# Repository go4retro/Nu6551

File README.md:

# Nu6551 

An implementation of the MOS 6551 Asynchronous Communications Interface Adapter (ACIA) that utilizes a small CPLD and an Atmel AVR ATMEGA88/168 microcontroller

## Introduction

## Technical Details

## License
Copyright (C) 2018-20  RETRO Innovations

These files are free designs; you can redistribute them and/or modify
them under the terms of the Creative Commons Attribution-ShareAlike 
4.0 International License.

You should have received a copy of the license along with this
work. If not, see <http://creativecommons.org/licenses/by-sa/4.0/>.

These files are distributed in the hope that they will be useful,
but WITHOUT ANY WARRANTY; without even the implied warranty of
MERCHANTABILITY or FITNESS FOR A PARTICULAR PURPOSE.  See the
license for more details.

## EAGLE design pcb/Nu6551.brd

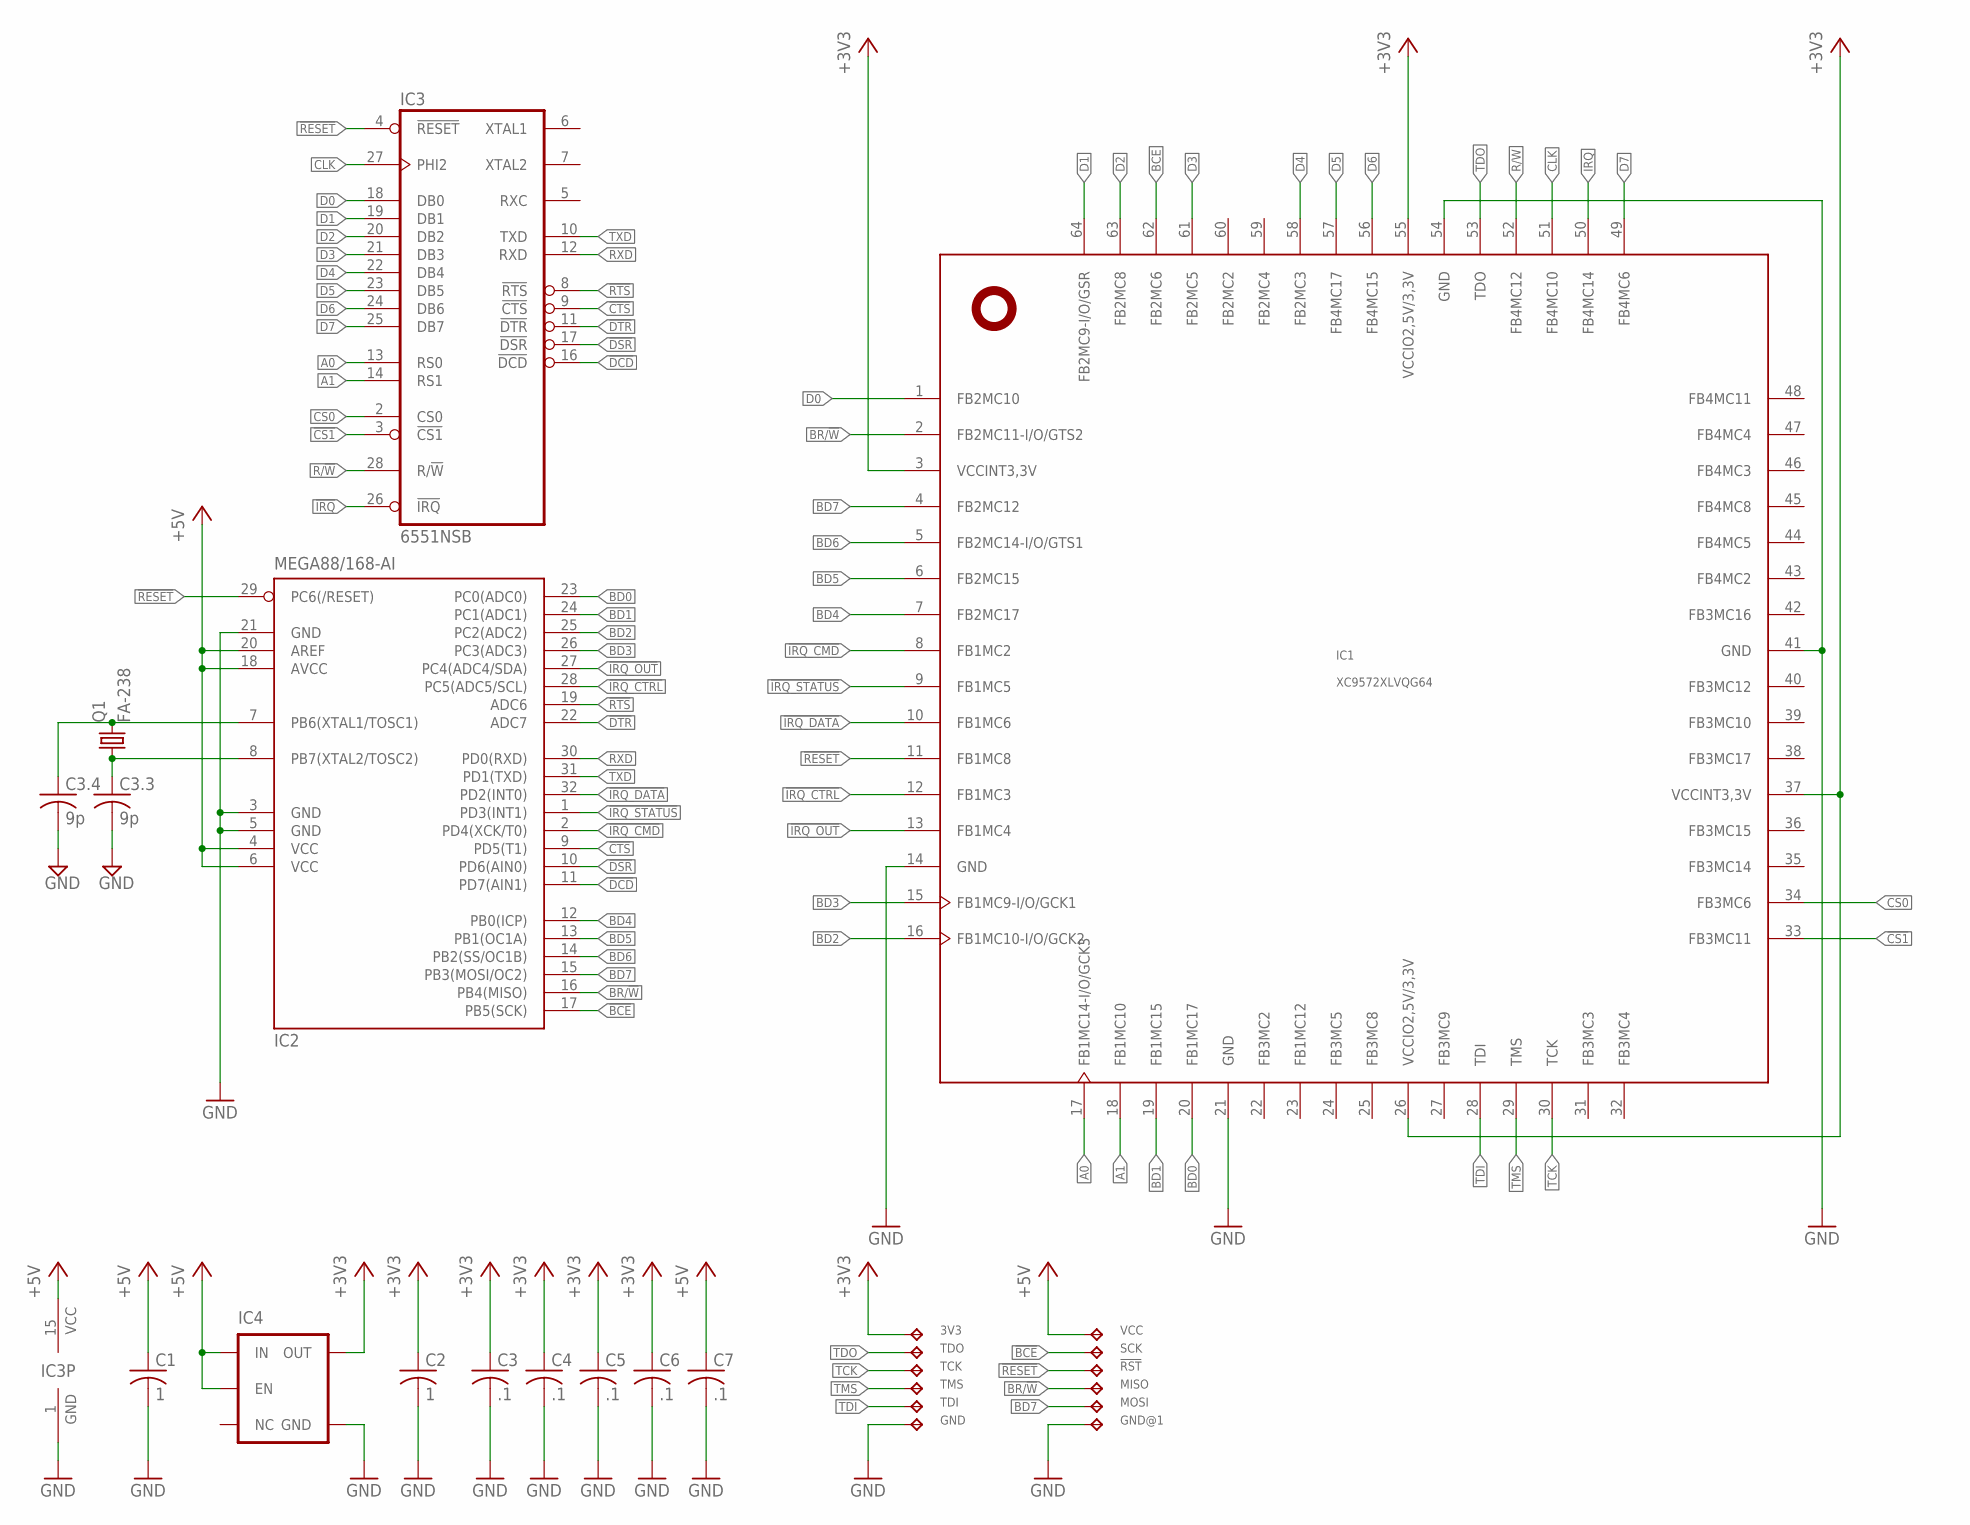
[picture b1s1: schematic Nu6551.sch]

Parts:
3V3: TPTP10R; TP10R
!RST: TPTP10R; TP10R
C1, C2: 1; C0402
C3, C4, C5, C6, C7: .1; C0402
C3.3, C3.4: 9p; C0402
GND: TPTP10R; TP10R
GND@1: TPTP10R; TP10R
IC1: XC9572XLVQG64; VQFP64
IC2: MEGA88/168-AI; TQFP32-08
IC3: 6551NSB; DIL28-SMD-REVERSE
IC4: V_REG_TPS76433SOT23-5; SOT23-5
MISO: TPTP10R; TP10R
MOSI: TPTP10R; TP10R
Q1: FA-238; ASE
SCK: TPTP10R; TP10R
TCK: TPTP10R; TP10R
TDI: TPTP10R; TP10R
TDO: TPTP10R; TP10R
TMS: TPTP10R; TP10R
VCC: TPTP10R; TP10R

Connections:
!BCE: IC1.62 (FB2MC6), IC2.17 (PB5(SCK)), SCK.TP
!CS1: IC1.33 (FB3MC11), IC3.3 (!CS1)
!CTS: IC2.9 (PD5(T1)), IC3.9 (!CTS)
!DCD: IC2.11 (PD7(AIN1)), IC3.16 (!DCD)
!DSR: IC2.10 (PD6(AIN0)), IC3.17 (!DSR)
!DTR: IC2.22 (ADC7), IC3.11 (!DTR)
!IRQ: IC1.50 (FB4MC14), IC3.26 (!IRQ)
!IRQ_CMD: IC1.8 (FB1MC2), IC2.2 (PD4(XCK/T0))
!IRQ_CTRL: IC1.12 (FB1MC3), IC2.28 (PC5(ADC5/SCL))
!IRQ_DATA: IC1.10 (FB1MC6), IC2.32 (PD2(INT0))
!IRQ_OUT: IC1.13 (FB1MC4), IC2.27 (PC4(ADC4/SDA))
!IRQ_STATUS: IC1.9 (FB1MC5), IC2.1 (PD3(INT1))
!RESET: !RST.TP, IC1.11 (FB1MC8), IC2.29 (PC6(/RESET)), IC3.4 (!RESET)
!RTS: IC2.19 (ADC6), IC3.8 (!RTS)
+3V3: 3V3.TP, C2.1, C3.1, C4.1, C5.1, C6.1, IC1.3 (VCCINT3,3V), IC1.26 (VCCIO2,5V/3,3V), IC1.37 (VCCINT3,3V), IC1.55 (VCCIO2,5V/3,3V), IC4.5 (OUT)
+5V: C1.1, C7.1, IC2.4 (VCC), IC2.6 (VCC), IC2.18 (AVCC), IC2.20 (AREF), IC3.15 (VCC), IC4.1 (IN), IC4.3 (EN), VCC.TP
A0: IC1.17 (FB1MC14-I/O/GCK3), IC3.13 (RS0)
A1: IC1.18 (FB1MC10), IC3.14 (RS1)
BD0: IC1.20 (FB1MC17), IC2.23 (PC0(ADC0))
BD1: IC1.19 (FB1MC15), IC2.24 (PC1(ADC1))
BD2: IC1.16 (FB1MC10-I/O/GCK2), IC2.25 (PC2(ADC2))
BD3: IC1.15 (FB1MC9-I/O/GCK1), IC2.26 (PC3(ADC3))
BD4: IC1.7 (FB2MC17), IC2.12 (PB0(ICP))
BD5: IC1.6 (FB2MC15), IC2.13 (PB1(OC1A))
BD6: IC1.5 (FB2MC14-I/O/GTS1), IC2.14 (PB2(SS/OC1B))
BD7: IC1.4 (FB2MC12), IC2.15 (PB3(MOSI/OC2)), MOSI.TP
BR/!W: IC1.2 (FB2MC11-I/O/GTS2), IC2.16 (PB4(MISO)), MISO.TP
CLK: IC1.51 (FB4MC10), IC3.27 (PHI2)
CS0: IC1.34 (FB3MC6), IC3.2 (CS0)
D0: IC1.1 (FB2MC10), IC3.18 (DB0)
D1: IC1.64 (FB2MC9-I/O/GSR), IC3.19 (DB1)
D2: IC1.63 (FB2MC8), IC3.20 (DB2)
D3: IC1.61 (FB2MC5), IC3.21 (DB3)
D4: IC1.58 (FB2MC3), IC3.22 (DB4)
D5: IC1.57 (FB4MC17), IC3.23 (DB5)
D6: IC1.56 (FB4MC15), IC3.24 (DB6)
D7: IC1.49 (FB4MC6), IC3.25 (DB7)
GND: C1.2, C2.2, C3.2, C3.3.2, C3.4.2, C4.2, C5.2, C6.2, C7.2, GND.TP, GND@1.TP, IC1.14 (GND), IC1.21 (GND), IC1.41 (GND), IC1.54 (GND), IC2.3 (GND), IC2.5 (GND), IC2.21 (GND), IC3.1 (GND), IC4.2 (GND), Q1.2 (GND), Q1.4 (GND)
unnamed: C3.3.1, IC2.8 (PB7(XTAL2/TOSC2)), Q1.1
unnamed: C3.4.1, IC2.7 (PB6(XTAL1/TOSC1)), Q1.3 (2)
R/!W: IC1.52 (FB4MC12), IC3.28 (R/!W)
RXD: IC2.30 (PD0(RXD)), IC3.12 (RXD)
TCK: IC1.30 (TCK), TCK.TP
TDI: IC1.28 (TDI), TDI.TP
TDO: IC1.53 (TDO), TDO.TP
TMS: IC1.29 (TMS), TMS.TP
TXD: IC2.31 (PD1(TXD)), IC3.10 (TXD)

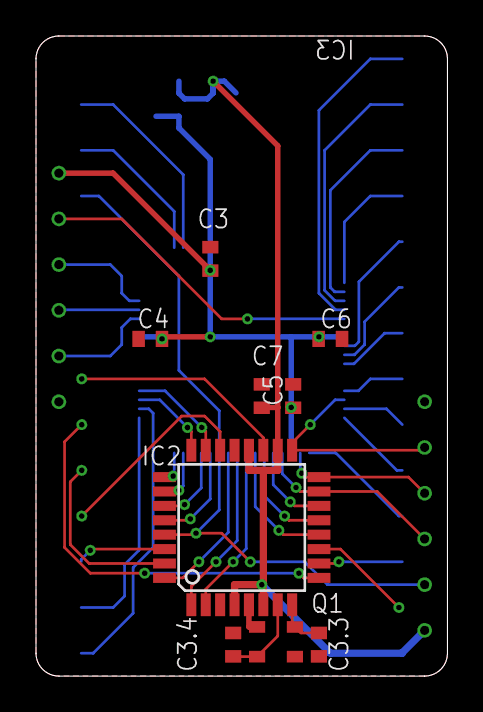
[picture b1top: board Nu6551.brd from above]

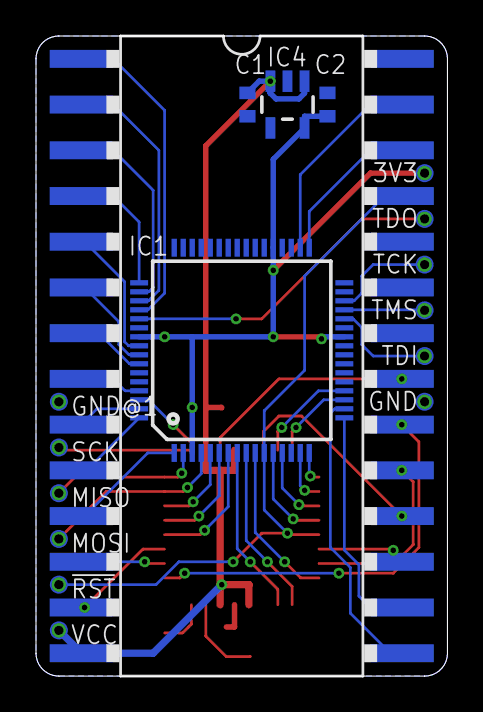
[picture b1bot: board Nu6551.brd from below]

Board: 2 copper layers, 22.9 x 35.6 mm, 26 parts (16 on the bottom side), 47 nets.

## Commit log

2021-01-07 Add PCB (untested as yet)
2021-02-22 Added default AVR project

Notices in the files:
parts and their libraries:
SparkFun: Licensing: CC v3.0 Share-Alike You are welcome to use this library for commercial purposes.
